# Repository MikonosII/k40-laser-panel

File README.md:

# K40 laser panel

A touchscreen control panel and controller upgrade for the K40 CO₂ laser. A 5" ESP32-P4 touchscreen
sits on the front of the machine. The K40 runs **grblHAL** on a BTT SKR board, and **LightBurn streams
over Wi-Fi** through the panel, so no USB cable runs to the PC.

```
LightBurn ──Wi-Fi──► 5" panel (ESP32-P4) ──serial──► BTT SKR (grblHAL) ──► K40 motors + laser PSU
                      ▲ touch: status, pause/stop, overrides, jog, test fire, tube current
```

> [!WARNING]
> **Early release.** The firmware compiles, but it's being tested on its first machine now. Check each
> step against your own K40, and do the first tests with the K40's **Laser** switch off.
>
> A K40 runs at around 20 kV and can start fires. Unplug it and wait before working inside, never
> defeat the lid or water interlocks, and never leave it running unattended.

*Screen designs: Status, Jog, Laser, Alarms, Setup and Jobs. The Jobs screen and the job preview
on Status are in the [beta branch](#beta-run-jobs-from-the-panel).*

## What it does

- **Status at a glance:** state, position, speed, laser power, live tube current (mA), job time.
- **Control from the machine:** pause, resume, stop, feed and power overrides, air assist, jog,
  home, set origin, timed test fire, low-power pointer.
- **Shares control with LightBurn:** the panel's buttons work mid-job without corrupting LightBurn's
  stream.
- **Safety:**
  - Lid and water status (optional second switches).
  - A software power cap, and an automatic shut-off if tube current goes over a limit (optional
    sensor).
  - PIN lock for Setup and test fire.
- **Easy to set up and update:** Wi-Fi, LightBurn PC and limits are set on the touchscreen.
  Firmware updates go on from a microSD card.
- **Plain-English alarms**, laser on-time (tube hours) and screen sleep.

## Hardware

| Part | Where | Notes |
|---|---|---|
| Elecrow CrowPanel Advanced 5" **ESP32-P4** (800×480, without camera) | [Amazon](https://www.amazon.com/dp/B0GLGWJP8B) | Used in portrait. Wi-Fi via its on-board ESP32-C6. Get the **P4** model, not the ESP32-S3 "Advance" |
| BTT **SKR Mini E3 V3** | [Amazon](https://www.amazon.com/dp/B0DFH6HDJ4) | Runs grblHAL. Its TMC2209 drivers run the K40's steppers |
| *or* BTT **SKR 3** with TMC2209 drivers | [Amazon](https://www.amazon.com/dp/B0CD7SFRGC) | Ships with an STM32H723 or H743 chip. This repo's build is for the **H723**, so check the chip |
| Panel mounting plate (laser-cut, e.g. 3 mm acrylic) | [Cut file](hardware/panel-mount/README.md) | Holds the panel on the K40. A good first job for the upgraded laser |
| Mean Well **RD-125B** (24 V + 5 V) | [Amazon](https://www.amazon.com/dp/B005T9JN6E) | 24 V for the SKR, 5 V for the panel |
| 1N5819 diode | [Amazon](https://www.amazon.com/dp/B079KG1TN2) | Laser enable, see [wiring](docs/wiring.md#laser-psu) |
| JST-XH 2.54 mm kit with pre-crimped leads | [Amazon](https://www.amazon.com/dp/B08G17QHSD) | Panel UART3-IN plug (4-pin) |
| *Optional:* second lid switch, second water-flow switch | | Lid and water status on the panel |
| *Optional:* [tube current sensor](hardware/current-sensor-pcb/README.md) + [Grove cable](https://www.amazon.com/dp/B01CNZ9RJO) | | Live mA readout and over-current shut-off |

Listings change, so check the model before buying. These aren't affiliate links.

## Getting started

1. **Wire it:** [docs/wiring.md](docs/wiring.md) has the full diagram plus the laser PSU, lid and water details.
2. **Flash the SKR and the panel:** [docs/install.md](docs/install.md). Both are ready-made files.
   The SKR flashes straight from a microSD card. The panel needs one install over USB from your
   browser, then updates from a microSD card too.
3. **Power up and check the link:** the panel's header should show *Idle*.
4. **Set it up on the touchscreen:** Wi-Fi, your LightBurn PC's IP and the power limits.
   See [docs/using.md](docs/using.md).
5. **Connect LightBurn** as a GRBL device over the network: the panel's IP, port 23.

Something not working? Check [docs/troubleshooting.md](docs/troubleshooting.md).

## Tube current sensor (optional)

An isolated INA226 board goes in series with the tube's return wire and plugs into the panel's I2C
port. You get the real tube current on screen, a warning above one limit, and an automatic laser
shut-off above another (20 mA by default).
- [Single-board PCB](hardware/current-sensor-pcb/README.md): Gerbers, BOM and placement files for
  JLCPCB assembly, plus a Digi-Key BOM for building it yourself.
- [Two-module version](docs/tube-current-sensor.md): built from off-the-shelf breakout boards.

## Beta: run jobs from the panel

The [`feature/sd-jobs`](https://github.com/MikonosII/k40-laser-panel/tree/feature/sd-jobs) branch adds:
- **Panel jobs:** upload G-code from a browser (LightBurn's *Save GCode*), store it on the panel's SD
  card, and run it from a new **Jobs** screen. A Wi-Fi drop or a sleeping PC can't interrupt the job.
- **Preview:** a picture of the job's laser path with the head's live position.
- **History:** the last 20 jobs, with time, run time and peak tube current.

It merges into `main` once it's been tested on a machine.

## Repository layout

| Path | What |
|---|---|
| `main/` | Panel firmware (ESP-IDF 5.5, C++, LVGL 9) |
| `release/` | Ready-made panel images (`firmware.bin` for SD updates, `k40-panel-full-*.bin` for the first USB install) and grblHAL builds |
| `grblhal/` | grblHAL build for the SKR Mini E3 V3 (and `skr3/` for the SKR 3), with settings and source build scripts |
| `hardware/current-sensor-pcb/` | KiCad board, fab files, BOMs, printed enclosure |
| `hardware/panel-mount/` | Laser-cut mounting plate for the 5" panel |
| `hardware/lid-stay/` | Printed magnetic lid stop that holds the lid at a set angle, for a LightBurn camera |
| `docs/` | Wiring, install, usage, troubleshooting, current sensor |

## Credits and license

Built on [grblHAL](https://github.com/grblHAL) (including the community
[STM32G0xx](https://github.com/mtaylor819/STM32G0xx) and [STM32H7xx](https://github.com/dresco/STM32H7xx)
drivers), [LVGL](https://lvgl.io), Espressif's [ESP-IDF](https://github.com/espressif/esp-idf) and
[esp_hosted](https://github.com/espressif/esp-hosted-mcu), and Elecrow's board examples.

- Panel firmware and docs: **MIT** ([LICENSE](LICENSE))
- Current sensor PCB: **CERN-OHL-P-2.0** ([LICENSE](hardware/current-sensor-pcb/LICENSE))
- grblHAL builds: **GPL-3.0**, like grblHAL itself ([COPYING](grblhal/COPYING))

No warranty. You are responsible for your own machine and safety.

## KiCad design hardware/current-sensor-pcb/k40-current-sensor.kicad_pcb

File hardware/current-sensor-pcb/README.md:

# Tube current sensor PCB

One small board that replaces the two-module build in
[docs/tube-current-sensor.md](../../docs/tube-current-sensor.md). It does the same job with the
same chips (INA226 + ADM3260) and needs no firmware changes: the panel finds it at address 0x40.

- 68 × 42 mm, 2 layers, 1.6 mm, four M3 holes (3.2 mm)
- All SMT parts on the top, sized for JLCPCB assembly
- 3 screw terminals (through-hole) you solder yourself
- 5.1 mm copper-free isolation gap between the panel side and the tube side

| Top | Bottom |
|---|---|
|  |  |

## Connections

| Terminal | Pin | Goes to |
|---|---|---|
| **J1** (3.5 mm, 4-pin) | SCL, SDA, 3V3, GND | Panel **I2C-OUT** (Grove cable, cut one end; red = 3V3, black = GND, yellow = SCL, white = SDA) |
| **J2** (3.5 mm, 2-pin) | +5V, GND | The 5 V supply (same 5 V that feeds the panel's UART3-IN pin 3) |
| **J3** (5.08 mm, 3-pin) | IN, OUT, EARTH | Tube cathode wire **IN → OUT**; EARTH to the chassis earth screw |

**J2 must have 5 V.** The isolated side runs at 5 V so the INA226 reads the ADM3260's logic
levels reliably, and the ADM3260 can only make 5 V from a 5 V input.

## Circuit

```
 Panel side                         |  barrier  |   Tube side (isolated)
                                    |           |
 J1 SCL ──┬─ R6 4.7k ─ 3V3          |   U2      |          VISO (5 V)
 J1 SDA ──┼─ R7 4.7k ─ 3V3          | ADM3260   |   R8/R9 4.7k pull-ups to VISO
          └── SCL2/SDA2 ────────────┤ I2C + DC/DC├── SCL1/SDA1 ─── U1 INA226 (0x40)
 J1 3V3 ── VDDP (C3 100n)           |           |   VISO ── U1 VS (C7 100n)
 J2 +5V ── VIN  (C1 10u, C2 100n)   |           |   VISO (C4 10u, C5 100n), VDDISO (C6 100n)
 PDIS ── GND (converter on)         |           |   VSEL: R4 30k / R5 10k  → 4.9 V
                                    |           |
                                    |           |   J3 IN ─┬─ R1 0.1 Ω ─┬─ J3 OUT (= isolated GND)
                                    |           |          ├ D1 SMAJ5.0CA ┤
                                    |           |          ├ R2 10 Ω ─ IN+ ┐ C8 100n
                                    |           |          │      R3 10 Ω ─ IN− ┘
                                    |           |          └ GDT1 200 V ── J3 EARTH
```

Full netlist (checked against the board file):

| Net | Pins |
|---|---|
| +3V3 | J1.3, U2.4 VDDP, C3, R6, R7 |
| +5V | J2.1, U2.9 VIN, C1, C2 |
| GND | J1.4, J2.2, U2.1/5/7/10, U2.8 PDIS, C1, C2, C3 |
| SCL_P / SDA_P | J1.1 / J1.2, U2.2 SCL2 / U2.3 SDA2, R6 / R7 |
| VISO | U2.12 VISO, U2.17 VDDISO, U1.6 VS, C4–C7, R4, R8, R9 |
| VSEL | U2.13, R4/R5 junction |
| SCL_I / SDA_I | U2.19 SCL1 / U2.18 SDA1, U1.5 / U1.4, R8 / R9 |
| GNDISO | J3.2 OUT, U2.11/14/16/20, U1.1 A1, U1.2 A0, U1.7 GND, U1.8 VBUS, R1, R3, R5, D1, C4–C7 |
| TUBE_IN | J3.1 IN, R1, R2, D1, GDT1 |
| INP_F / INN_F | U1.10 IN+ / U1.9 IN−, R2 / R3, C8 |
| EARTH | J3.3, GDT1 |

## Ordering from JLCPCB

1. Go to jlcpcb.com → **Order now** → upload **`fab/k40-current-sensor-gerbers.zip`**.
   Defaults are fine: 2 layers, 1.6 mm, any color, HASL lead-free (or ENIG).
2. Turn on **PCB Assembly**: Economic, **Top side**, quantity 2 or 5.
3. Upload **`fab/k40-current-sensor-bom.csv`** and **`fab/k40-current-sensor-cpl.csv`**.
4. On the parts page, confirm every line matched. **Check stock for U2 (ADM3260, C208558).** It's
   the scarce, pricey part (about $15). If JLC is out, choose **Global Sourcing** or pre-order
   it into your JLC parts library.
5. On the placement preview, check the **pin-1 dots on U1 and U2** line up with the dot on the
   silkscreen. The CPL already includes the 90° turn U1 needs in JLC's preview; rotate a part
   there only if it still lands off.
6. Order. A real order came to about **$123** at JLCPCB. Most of that is the ADM3260s (about
   $15 each) and JLC's $3-per-line fee for extended parts.

**OSH Park** also takes the same Gerber zip, but it doesn't assemble. You'd hand-solder the
SSOP-20 and the 0.5 mm-pitch VSSOP-10 yourself.

### Parts you solder yourself (not in the JLC BOM)

| Ref | Part | Phoenix # |
|---|---|---|
| J1 | Screw terminal, 4-pos, 3.5 mm | [PT 1,5/4-3,5-H 1984633](https://www.digikey.com/en/products/result?keywords=1984633) |
| J2 | Screw terminal, 2-pos, 3.5 mm | [PT 1,5/2-3,5-H 1984617](https://www.digikey.com/en/products/result?keywords=1984617) |
| J3 | Screw terminal, 3-pos, 5.08 mm | [MKDS 1,5/3-5,08 1715734](https://www.digikey.com/en/products/result?keywords=1715734) |
| – | Grove 4-pin cable (cut one end) to panel I2C-OUT | as in the module BOM |
| – | 4 × M3 **nylon** standoffs and screws | keeps the isolated side off the chassis |

## Assembled BOM (JLC)

| Ref | Value | Package | LCSC |
|---|---|---|---|
| U1 | INA226AIDGSR | VSSOP-10 | C49851 |
| U2 | ADM3260ARSZ | SSOP-20 | C208558 |
| R1 | 0.1 Ω 1 % 1 W (FOJAN FRM121WFR100TM) | 1206 | C7467250 |
| R2, R3 | 10 Ω | 0603 | C22859 |
| R4 | 30 kΩ | 0603 | C22984 |
| R5 | 10 kΩ | 0603 | C25804 |
| R6–R9 | 4.7 kΩ | 0603 | C23162 |
| C1, C4 | 10 µF 25 V | 0805 | C15850 |
| C2, C3, C5–C8 | 100 nF | 0603 | C14663 |
| D1 | SMAJ5.0CA bidirectional TVS | SMA | C10756 |
| GDT1 | 200 V gas discharge tube (Brightking 4532-201-LF; alt. 150 V 4532-151-LF C84727) | 1812 | C522630 |

Notes:
- R4 = 30 kΩ (a JLC basic part) sets VISO ≈ 4.9 V. The datasheet's 30.9 kΩ gives 5.0 V. Either works.
- R1 = 0.1 Ω matches the firmware's default shunt, so nothing needs changing in menuconfig.
- LCSC numbers were checked in October 2026; stock changes, so swap in an equivalent if a line
  shows out of stock.

## Build it yourself (Digi-Key or Arrow parts)

Cheaper than JLC assembly if you're OK hand-soldering fine-pitch SMT.

1. **Bare boards:** upload `fab/k40-current-sensor-gerbers.zip` to JLCPCB with **assembly off**
   (about $2–5 for 5 boards plus shipping), or to OSH Park (about $22 for 3, shipped in the US).
2. **Parts:** upload **`bom-digikey-arrow.csv`** to Digi-Key's BOM Manager (myLists → Upload) or
   Arrow's BOM tool. The resistors and capacitors carry Digi-Key **cut-tape** part numbers
   (the `CT-ND` / `-1-ND` ones), so you can buy 10 instead of a 5,000-piece reel. If any line
   still matches a reel, switch its packaging to **Cut Tape**. The other parts are matched by
   manufacturer part number, which Arrow also accepts. Quantities are
   for **2 boards**, with 10 of each small resistor and capacitor because they're easy to lose.
   Expect roughly $45–60 total; most of that is the two ADM3260s (about $13–16 each).
3. **Solder order:** U1 and U2 first (flux, tack one corner pin, check alignment, drag-solder,
   then wick off bridges), then the 0603/0805 parts, R1, D1, GDT1, and the terminals last.
   U1's pins are 0.5 mm apart, so use plenty of flux and a magnifier.
4. **Check before connecting the panel:** power J2 with 5 V only, and measure about 4.9 V between
   C4's two pads (isolated side). Then connect J1 and look for *Current sensor connected* on Setup.

GDT1 here is the Yageo 4532-231-LF (230 V); any 1812-size GDT from 150 to 250 V fits the same pads.

## Enclosure

A 3D-printable two-part box is in [`enclosure/`](enclosure/README.md) (STL files plus the OpenSCAD source).

## Install

- Mount on nylon standoffs, away from the HV lead, with the **TUBE SIDE** toward the laser PSU.
- Earth lead from **J3 EARTH** to the chassis earth screw, as short as you can make it.
- Wiring and safety rules are the same as the module build:
  [docs/tube-current-sensor.md](../../docs/tube-current-sensor.md#safety).

## Files

| Path | What |
|---|---|
| `k40-current-sensor.kicad_pcb` / `.kicad_pro` | KiCad 7 board (opens in KiCad 7 or 8) |
| `fab/k40-current-sensor-gerbers.zip` | Gerbers and drill files for any fab |
| `fab/k40-current-sensor-bom.csv`, `-cpl.csv` | JLCPCB assembly files |
| `drc.rpt` | KiCad DRC: 0 clearance errors, 0 unconnected. Only notes are the terminal silkscreen past the board edge and "library not in table" |
| `tools/` | The scripts that generated the board (`parts.py` is the parts list and netlist) |

To regenerate after editing `tools/parts.py`:

```bash
cd tools
python3 build.py place                 # board + Specctra DSN
xvfb-run java -jar freerouting-1.9.0.jar -de board.dsn -do board.ses -mp 40
python3 build.py finish                # import routes, pour grounds
python3 export.py                      # Gerbers, BOM, CPL
```

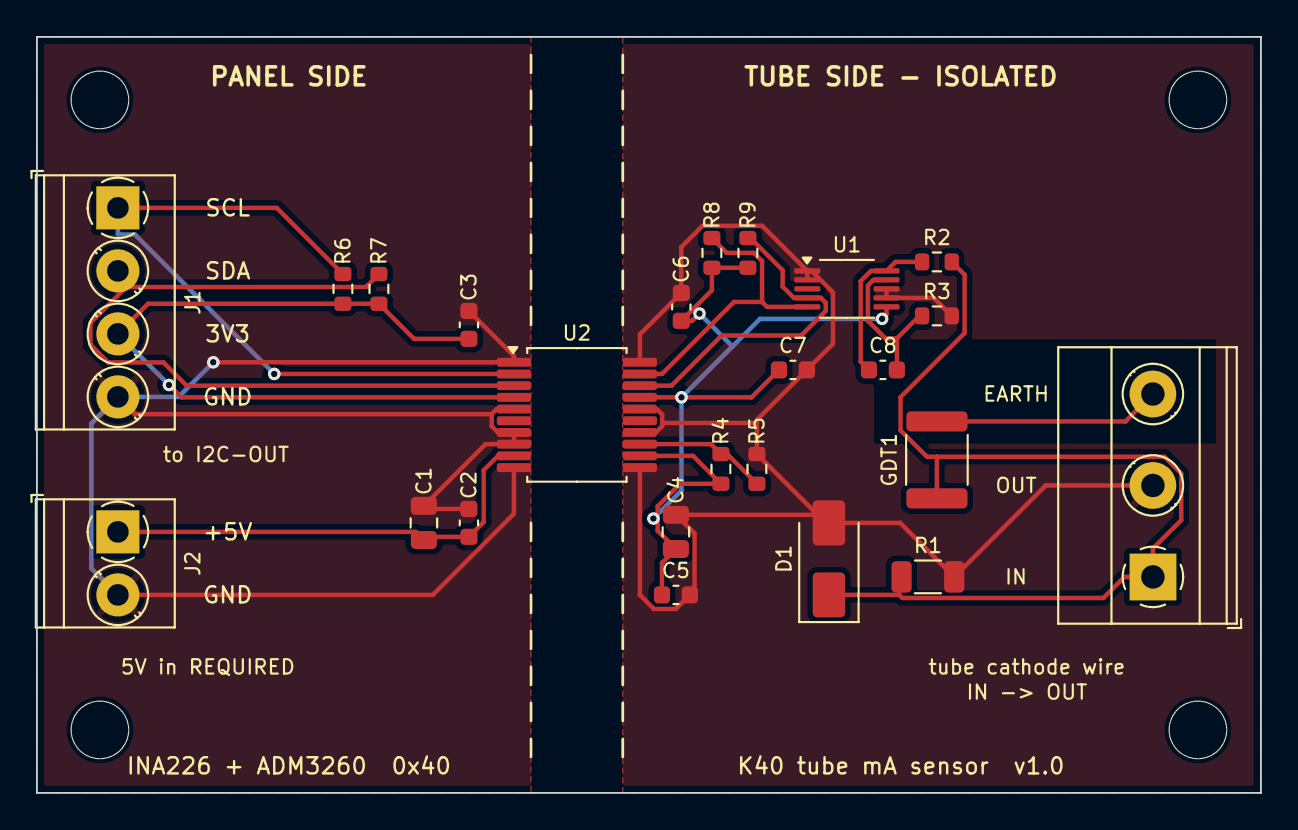
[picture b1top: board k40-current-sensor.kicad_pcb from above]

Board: 2 copper layers, 68.0 x 42.0 mm, 28 parts (0 on the bottom side), 14 nets.

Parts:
C1, C4: 10uF 25V; C_0805_2012Metric
C2, C3, C5, C6, C7, C8: 100nF; C_0603_1608Metric
D1: SMAJ5.0CA; D_SMA
GDT1: GDT 230V 1812; R_1812_4532Metric
H1, H2, H3, H4: MountingHole_3.2mm_M3
J1: I2C to panel; TerminalBlock_Phoenix_PT-1,5-4-3.5-H_1x04_P3.50mm_Horizontal
J2: 5V in; TerminalBlock_Phoenix_PT-1,5-2-3.5-H_1x02_P3.50mm_Horizontal
J3: Tube return; TerminalBlock_Phoenix_MKDS-1,5-3-5.08_1x03_P5.08mm_Horizont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
R1: 0.1R 1% 1206 1W; R_1206_3216Metric
R2, R3: 10R; R_0603_1608Metric
R4: 30k; R_0603_1608Metric
R5: 10k; R_0603_1608Metric
R6, R7, R8, R9: 4.7k; R_0603_1608Metric
U1: INA226AIDGSR; VSSOP-10_3x3mm_P0.5mm
U2: ADM3260ARSZ; SSOP-20_5.3x7.2mm_P0.65mm

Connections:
+3V3: C3.1, J1.3, R6.1, R7.1, U2.4
+5V: C1.1, C2.1, J2.1, U2.9
EARTH: GDT1.2, J3.3
GND: C1.2, C2.2, C3.2, J1.4, J2.2, U2.1, U2.5, U2.7, U2.8, U2.10
GNDISO: C4.2, C5.2, C6.2, C7.2, D1.2, J3.2, R1.2, R3.2, R5.2, U1.1, U1.2, U1.7, U1.8, U2.11, U2.14, U2.16, U2.20
INN_F: C8.2, R3.1, U1.9
INP_F: C8.1, R2.1, U1.10
SCL_I: R8.2, U1.5, U2.19
SCL_P: J1.1, R6.2, U2.2
SDA_I: R9.2, U1.4, U2.18
SDA_P: J1.2, R7.2, U2.3
TUBE_IN: D1.1, GDT1.1, J3.1, R1.1, R2.2
VISO: C4.1, C5.1, C6.1, C7.1, R4.1, R8.1, R9.1, U1.6, U2.12, U2.17
VSEL: R4.2, R5.1, U2.13

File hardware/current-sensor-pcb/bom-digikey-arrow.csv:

Quantity,Manufacturer Part Number,Manufacturer,Description,Customer Reference,Qty per board
2,INA226AIDGSR,Texas Instruments,"Current/power monitor, I2C, VSSOP-10",U1,1
2,ADM3260ARSZ,Analog Devices,"Isolated I2C + isoPower, SSOP-20",U2,1
10,RL1206FR-070R1L,YAGEO,0.1 ohm 1% 1206 current sense,R1,1
10,RC0603FR-0710RL,YAGEO,10 ohm 1% 0603,"R2,R3",2
10,RC0603FR-0730KL,YAGEO,30k 1% 0603,R4,1
10,RC0603FR-0710KL,YAGEO,10k 1% 0603,R5,1
10,RC0603FR-074K7L,YAGEO,4.7k 1% 0603,"R6,R7,R8,R9",4
10,CL21A106KAYNNNE,Samsung,10uF 25V X5R 0805,"C1,C4",2
12,CL10B104KB8NNNC,Samsung,100nF 50V X7R 0603,"C2,C3,C5,C6,C7,C8",6
2,SMAJ5.0CA,Littelfuse,"TVS bidirectional 5V, SMA",D1,1
2,4532-231-LF,YAGEO,"Gas discharge tube 230V, 1812 (4532)",GDT1,1
2,1984633,Phoenix Contact,"Terminal block 4-pos 3.5mm (PT 1,5/4-3,5-H)",J1,1
2,1984617,Phoenix Contact,"Terminal block 2-pos 3.5mm (PT 1,5/2-3,5-H)",J2,1
2,1715734,Phoenix Contact,"Terminal block 3-pos 5.08mm (MKDS 1,5/3-5,08)",J3,1
